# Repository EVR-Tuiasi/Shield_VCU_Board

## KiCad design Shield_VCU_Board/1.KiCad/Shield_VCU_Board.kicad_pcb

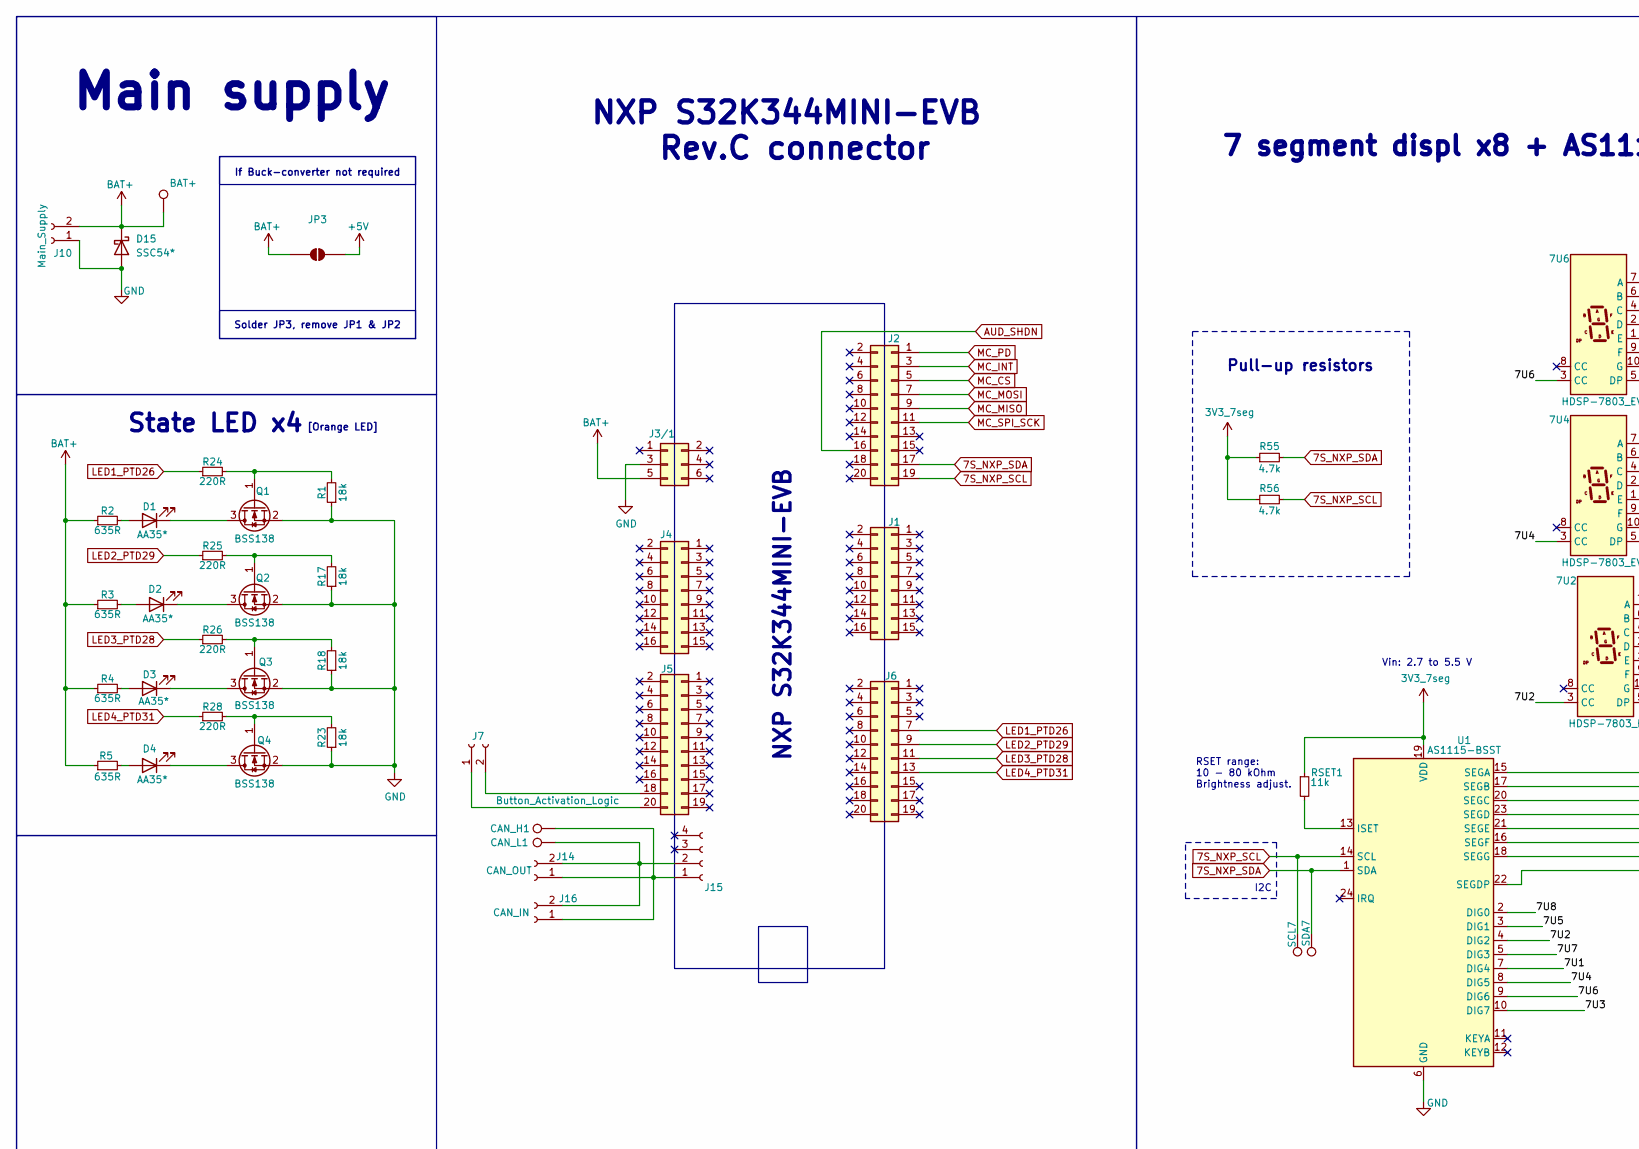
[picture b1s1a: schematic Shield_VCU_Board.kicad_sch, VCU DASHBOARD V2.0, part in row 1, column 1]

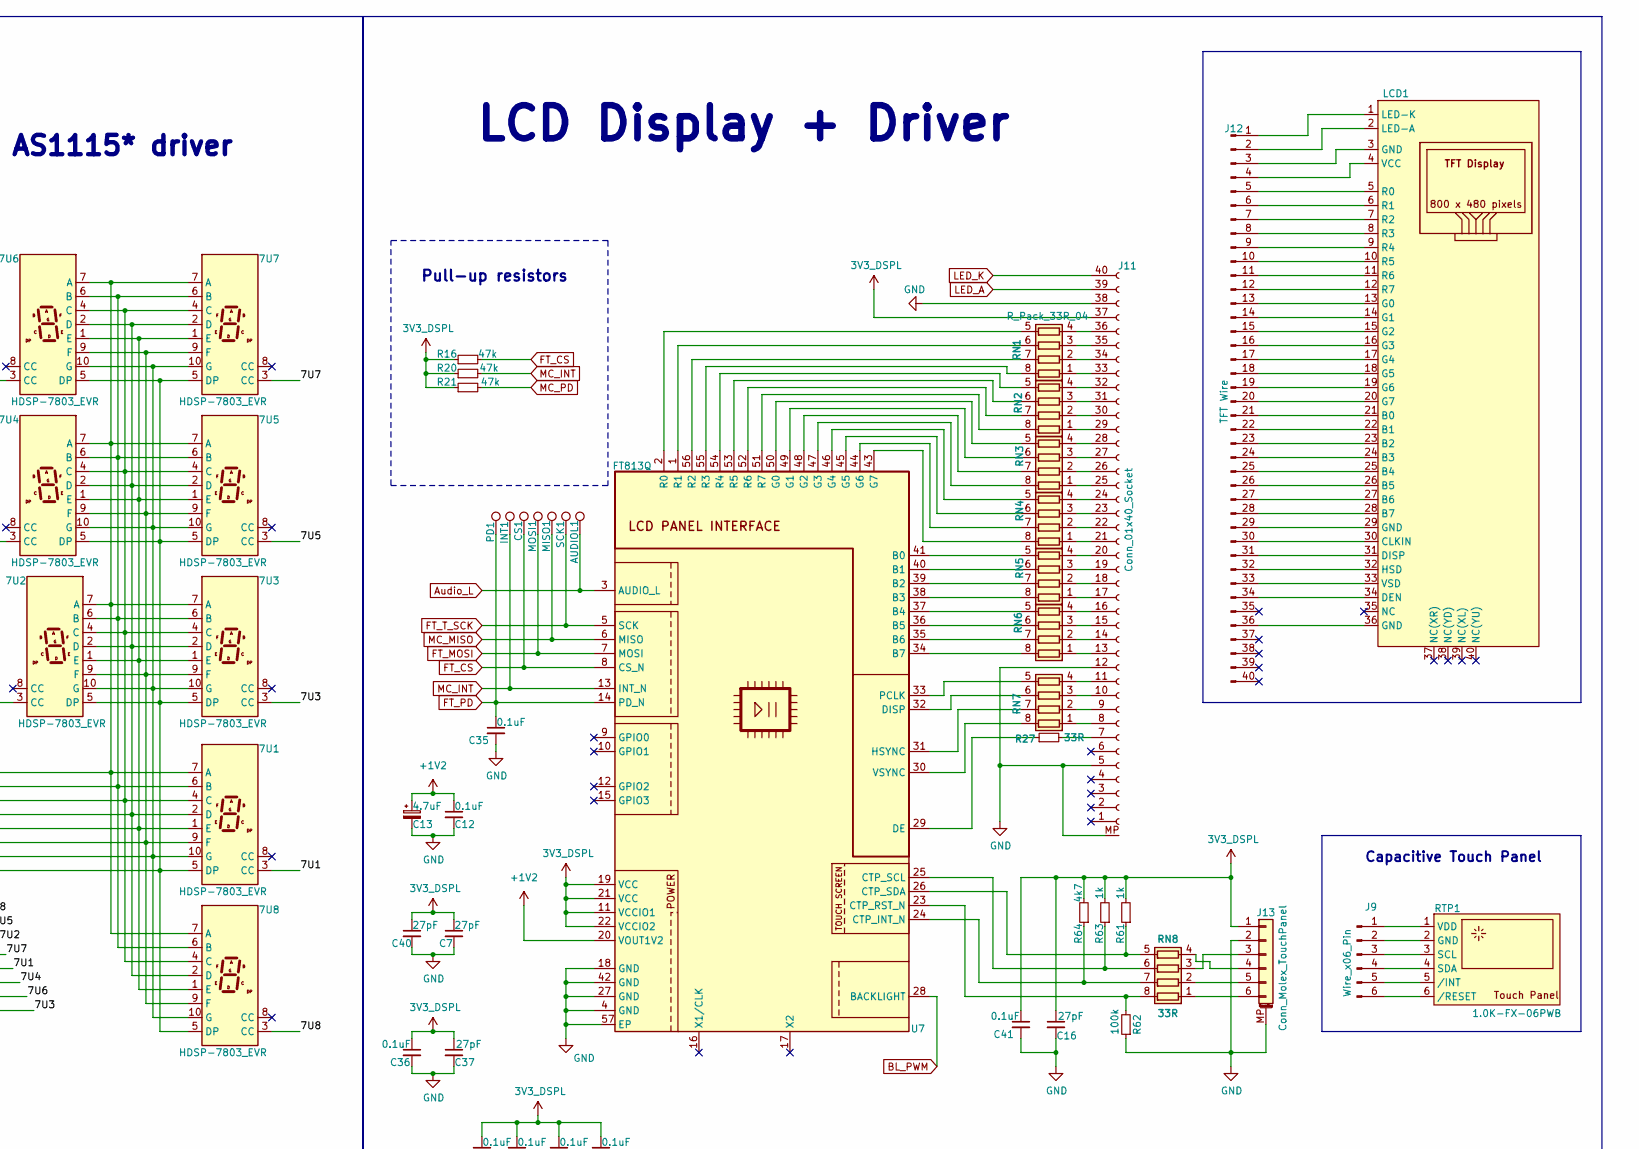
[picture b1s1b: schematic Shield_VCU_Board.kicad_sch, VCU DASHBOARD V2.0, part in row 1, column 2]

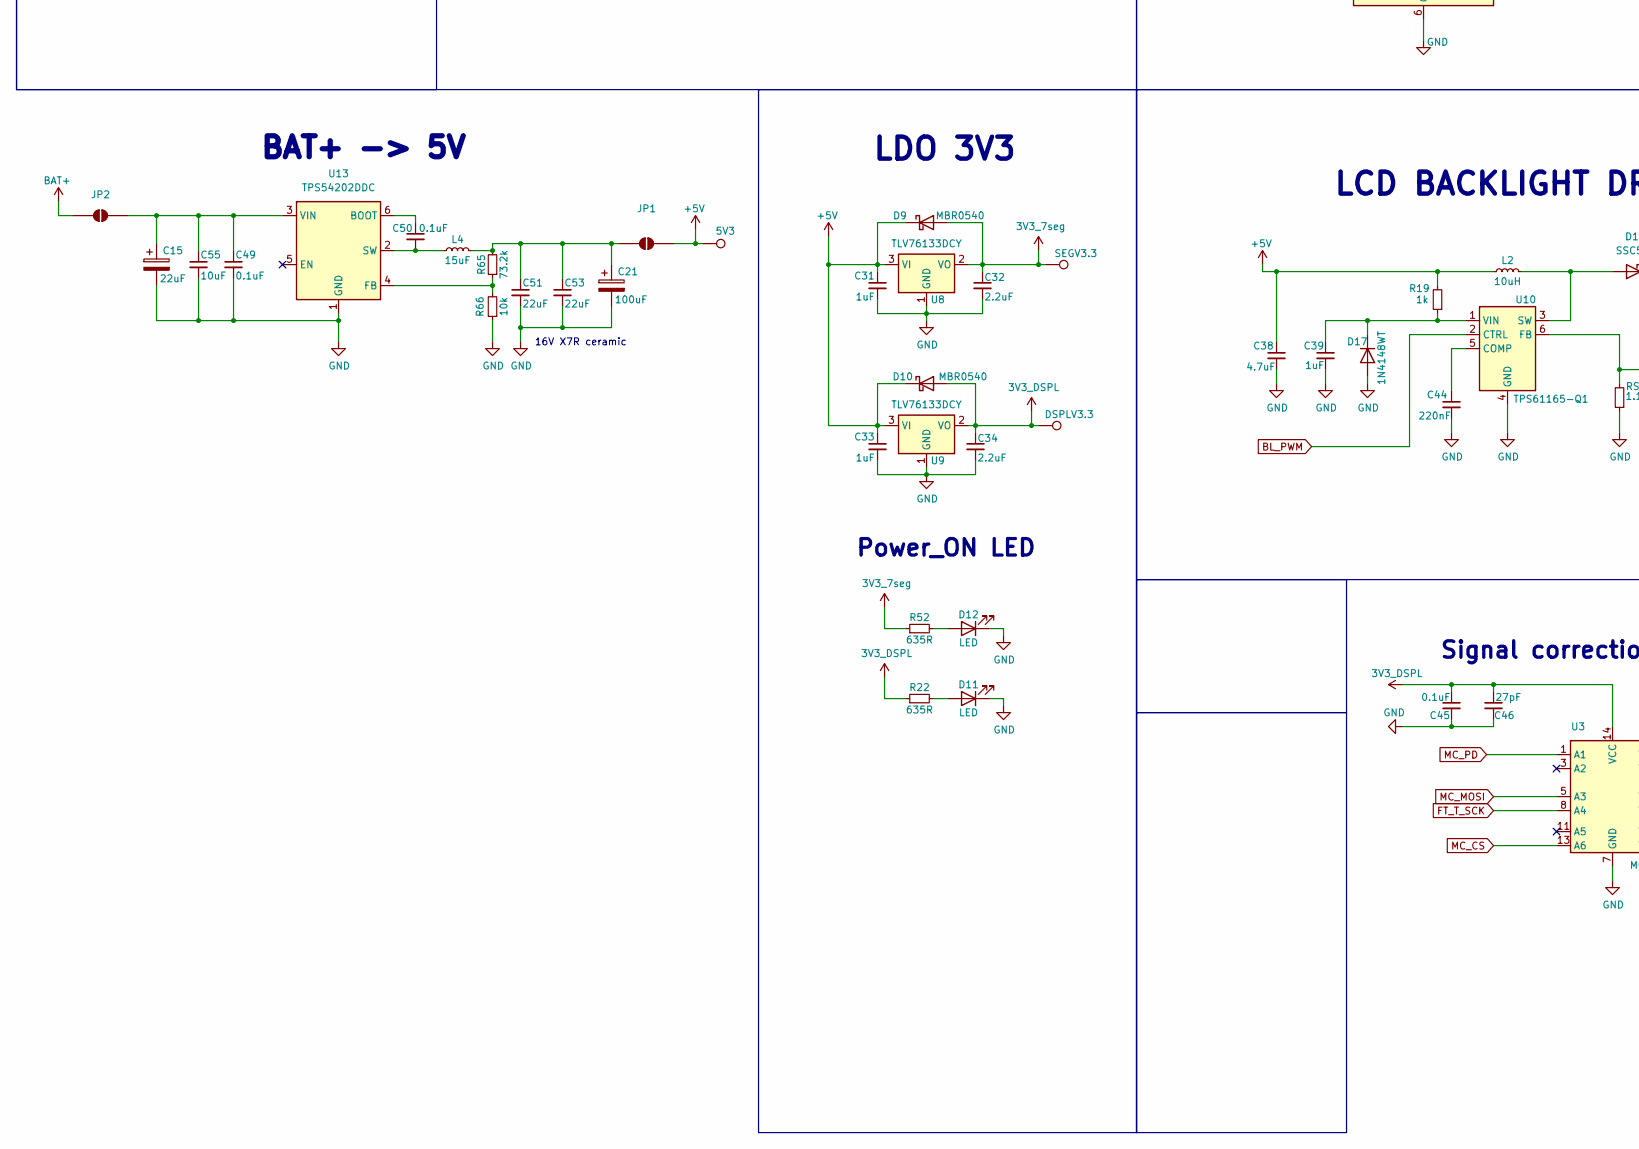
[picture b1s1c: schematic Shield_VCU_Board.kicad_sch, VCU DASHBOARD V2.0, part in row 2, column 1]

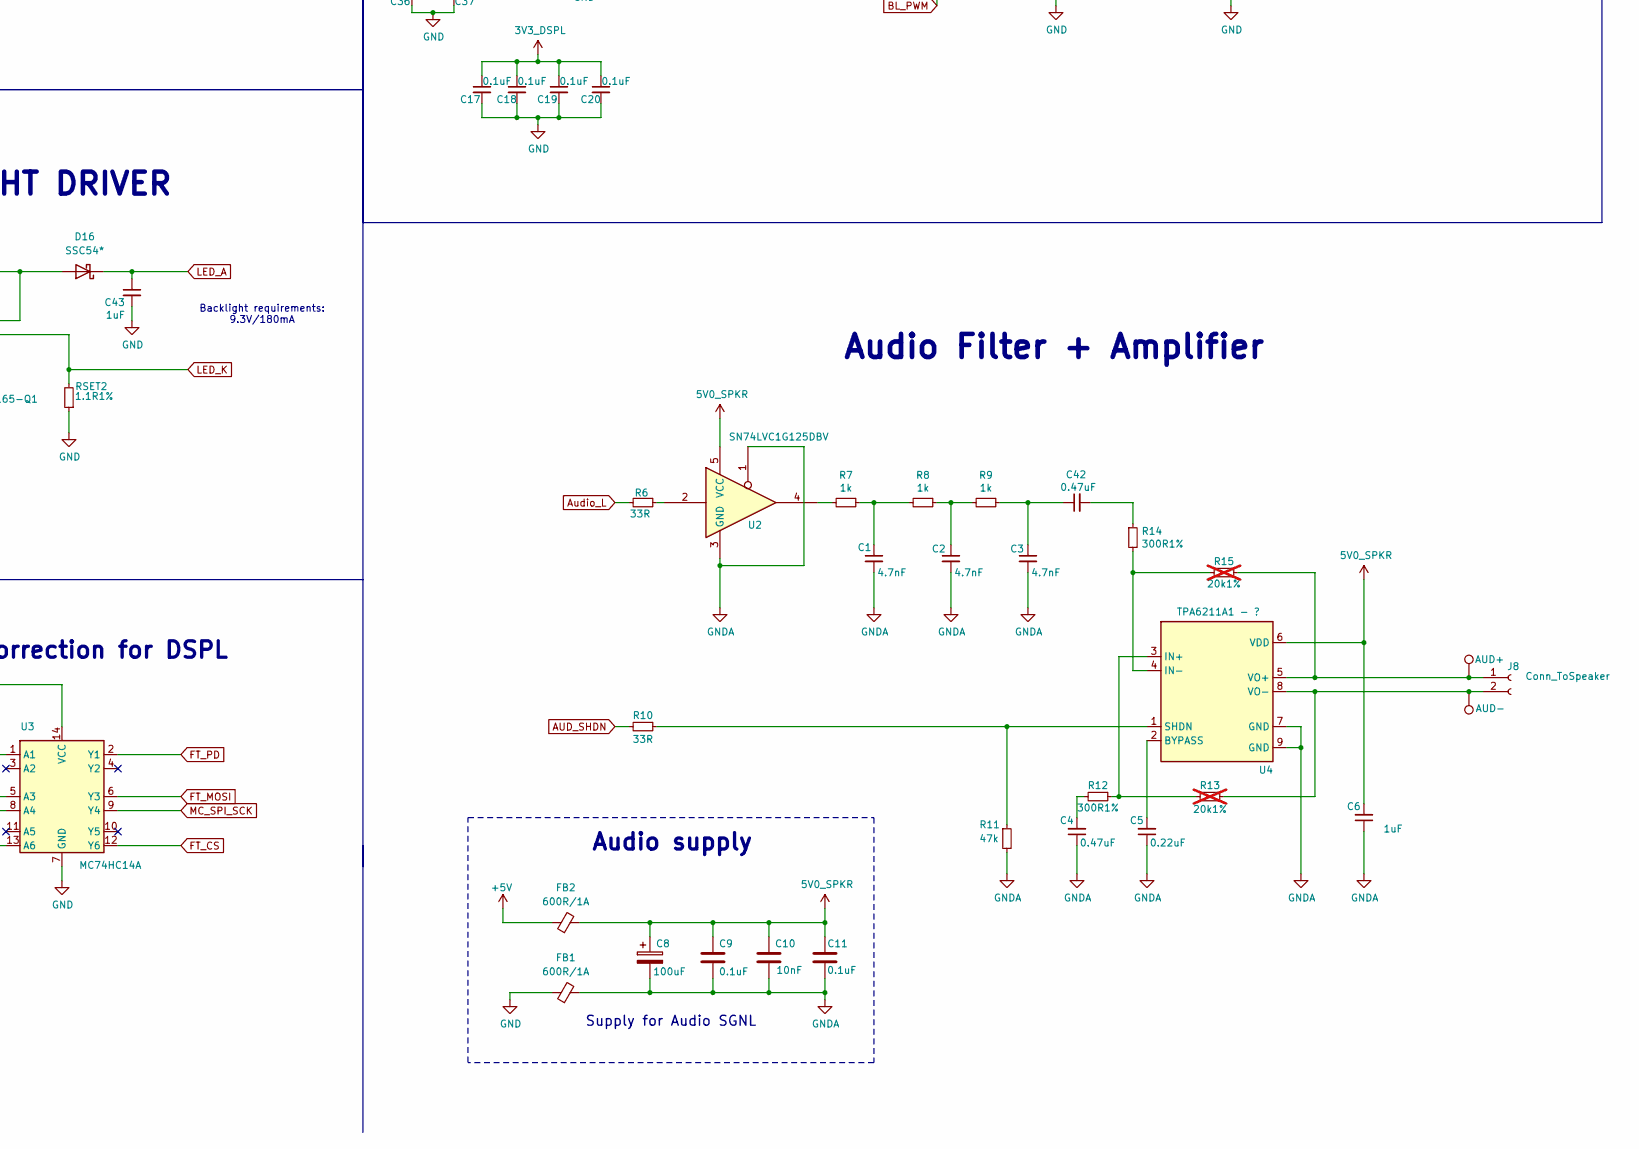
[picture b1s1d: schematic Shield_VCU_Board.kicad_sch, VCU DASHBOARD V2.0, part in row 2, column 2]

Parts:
5V3: 5V3; TestPoint_Pad_D1.0mm
7U1, 7U2, 7U3, 7U4, 7U5, 7U6, 7U7, 7U8: HDSP-7803_EVR; T7DS052BC
AUD+01: AUD+; TestPoint_Pad_D1.0mm
AUD-01: AUD-; TestPoint_Pad_D1.0mm
AUDIOL1: TestPoint; TestPoint_Pad_D1.0mm
BAT+01: BAT+; TestPoint_Pad_D1.0mm
C1, C2, C3: 4.7nF; C_0805_2012Metric_Pad1.18x1.45mm_HandSolder
C4, C42: 0.47uF; C_0805_2012Metric_Pad1.18x1.45mm_HandSolder
C5: 0.22uF; C_0805_2012Metric_Pad1.18x1.45mm_HandSolder
C6, C31, C33, C39, C43: 1uF; C_0805_2012Metric_Pad1.18x1.45mm_HandSolder
C7, C16, C37, C40, C46: 27pF; C_0805_2012Metric_Pad1.18x1.45mm_HandSolder
C8, C21: 100uF; CP_Elec_5x5.4
C9, C11, C12, C17, C18, C19, C20, C35, C36, C41, C45, C49, C50: 0.1uF; C_0805_2012Metric_Pad1.18x1.45mm_HandSolder
C10: 10nF; C_0805_2012Metric_Pad1.18x1.45mm_HandSolder
C13: 4.7uF; CP_EIA-2012-12_Kemet-R_HandSolder
C15: 22uF; CP_Elec_5x5.4
C32, C34: 2.2uF; C_0805_2012Metric_Pad1.18x1.45mm_HandSolder
C38: 4.7uF; C_0805_2012Metric_Pad1.18x1.45mm_HandSolder
C44: 220nF; C_0805_2012Metric_Pad1.18x1.45mm_HandSolder
C51, C53: 22uF; C_1210_3225Metric_Pad1.33x2.70mm_HandSolder
C55: 10uF; C_1210_3225Metric_Pad1.33x2.70mm_HandSolder
CAN_H1: TestPoint; TestPoint_Pad_D1.0mm
CAN_L1: TestPoint; TestPoint_Pad_D1.0mm
CS1: TestPoint; TestPoint_Pad_D1.0mm
D1, D2, D3, D4: AA35*; LED_Cree-PLCC4_3.2x2.8mm_CCW_Orange
D9, D10: MBR0540; D_SOD-123
D11, D12: LED; LED_0805_2012Metric
D15, D16: SSC54*; D_SMC
D17: 1N4148WT; D_SOD-123
DSPLV3.3: TestPoint; TestPoint_Pad_D1.0mm
FB1, FB2: 600R/1A; L_1206_3216Metric_Pad1.22x1.90mm_HandSolder
INT1: TestPoint; TestPoint_Pad_D1.0mm
J1, J4: Conn_02x08_Odd_Even; PinHeader_2x08_P2.54mm_Vertical_SMD
J2, J5, J6: Conn_02x10_Odd_Even; PinHeader_2x10_P2.54mm_Vertical_SMD
J3/1: NXP3; PinHeader_2x03_P2.54mm_Vertical_SMD
J7: Button_Activation_Logic; JST_PH_B2B-PH-K_1x02_P2.00mm_Vertical
J8: Conn_ToSpeaker; JST_PH_B2B-PH-K_1x02_P2.00mm_Vertical
J9: Wire_x06_Pin
J10: Main_Supply; JST_XH_B2B-XH-A_1x02_P2.50mm_Vertical
J11: Conn_01x40_Socket; Amphenol_F32Q-1A7x1-11040_1x40-1MP_P0.5mm_Horizontal
J12: TFT Wire
J13: Conn_Molex_TouchPanel; Molex_200528-0060_1x06-1MP_P1.00mm_Horizontal
J14: CAN_OUT; JST_PH_B2B-PH-K_1x02_P2.00mm_Vertical
J15: Conn_01x04_Socket; PinHeader_1x04_P2.54mm_Vertical
J16: CAN_IN; JST_PH_B2B-PH-K_1x02_P2.00mm_Vertical
JP1, JP2: SolderJumper_2_Open; SolderJumper-2_P1.3mm_Open_RoundedPad1.0x1.5mm
JP3: SolderJumper_2_Open; SolderJumper-2_P1.3mm_Open_TrianglePad1.0x1.5mm
L2: 10uH; L_Pulse_PA4340
L4: 15uF; L_Coilcraft_LPS4018
LCD1: LCD screen
MISO1: TestPoint; TestPoint_Pad_D1.0mm
MOSI1: TestPoint; TestPoint_Pad_D1.0mm
PD1: TestPoint; TestPoint_Pad_D1.0mm
Q1, Q2, Q3, Q4: BSS138; SOT-23
R1, R17, R18, R23: 18k; R_1206_3216Metric_Pad1.30x1.75mm_HandSolder
R2, R3, R4, R5, R22, R52: 635R; R_1206_3216Metric_Pad1.30x1.75mm_HandSolder
R6, R10: 33R; R_1206_3216Metric_Pad1.30x1.75mm_HandSolder
R7, R8, R9, R19, R61, R63: 1k; R_1206_3216Metric_Pad1.30x1.75mm_HandSolder
R11, R16, R20, R21: 47k; R_1206_3216Metric_Pad1.30x1.75mm_HandSolder
R12, R14: 300R1%; R_1206_3216Metric_Pad1.30x1.75mm_HandSolder
R13, R15: 20k1%; R_1206_3216Metric_Pad1.30x1.75mm_HandSolder; not fitted
R24, R25, R26, R28: 220R; R_1206_3216Metric_Pad1.30x1.75mm_HandSolder
R27: 33R; R_0603_1608Metric_Pad0.98x0.95mm_HandSolder
R55, R56: 4.7k; R_1206_3216Metric_Pad1.30x1.75mm_HandSolder
R62: 100k; R_1206_3216Metric_Pad1.30x1.75mm_HandSolder
R64: 4k7; R_1206_3216Metric_Pad1.30x1.75mm_HandSolder
R65: 73.2k; R_1206_3216Metric_Pad1.30x1.75mm_HandSolder
R66: 10k; R_1206_3216Metric_Pad1.30x1.75mm_HandSolder
RN1, RN2, RN3, RN4, RN5, RN6, RN7: R_Pack_33R_04; R_Array_Convex_4x0402
RN8: 33R; R_Array_Convex_4x0402
RSET1: 11k; R_1206_3216Metric_Pad1.30x1.75mm_HandSolder
RSET2: 1.1R1%; R_1206_3216Metric_Pad1.30x1.75mm_HandSolder
RTP1: 1.0K-FX-06PWB
SCK1: TestPoint; TestPoint_Pad_D1.0mm
SCL7: TestPoint; TestPoint_Pad_D1.0mm
SDA7: TestPoint; TestPoint_Pad_D1.0mm
SEGV3.3: TestPoint; TestPoint_Pad_D1.0mm
U1: AS1115-BSST; QSOP-24_3.9x8.7mm_P0.635mm
U2: SN74LVC1G125DBV; SOT-23-5
U3: MC74HC14A; SOIC-14_3.9x8.7mm_P1.27mm
U4: TPA6211A1 - ?; SOP65P490X110-9L
U7: FT813Q; LFCSP-56-1EP_8x8mm_P0.5mm_EP6.6x6.6mm
U8, U9: TLV76133DCY; SOT-223-3_TabPin2
U10: TPS61165-Q1; SOT-23-6
U13: TPS54202DDC; SOT-23-6

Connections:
3V3_7seg: C32.1, D9.2 (A), R52.1, R55.1, R56.1, RSET1.1, SEGV3.3.1 (1_1), U1.19 (VDD), U8.2 (VO)
3V3_DSPL: C7.1, C16.1, C17.1, C18.1, C19.1, C20.1, C34.1, C36.1, C37.1, C40.1, C41.1, C45.1, C46.1, D10.2 (A), DSPLV3.3.1 (1_1), J11.37 (Pin_4), J13.1, R16.1, R20.1, R21.1, R22.1, R61.2, R63.2, R64.2, U3.14 (VCC), U7.11 (VCCIO1), U7.19 (VCC), U7.21 (VCC), U7.22 (VCCIO2), U9.2 (VO)
5V0_SPKR: C6.2, C8.1, C9.2, C10.2, C11.2, FB2.2, U2.5 (VCC), U4.6 (VDD)
7S_NXP_SCL: J2.19, R56.2, SCL7.1 (1_1), U1.14 (SCL)
7S_NXP_SDA: J2.17, R55.2, SDA7.1 (1_1), U1.1 (SDA)
+1V2: C12.1, C13.1, U7.20 (VOUT1V2)
+5V: 5V3.1 (1_1), C31.1, C33.1, C38.1, D9.1 (K), D10.1 (K), FB2.1, JP1.2 (B), JP3.2 (B), L2.1, R19.2, U8.3 (VI), U9.3 (VI)
/7U1: 7U1.3 (CC), U1.7 (DIG4)
/7U2: 7U2.3 (CC), U1.4 (DIG2)
/7U3: 7U3.3 (CC), U1.10 (DIG7)
/7U4: 7U4.3 (CC), U1.8 (DIG5)
/7U5: 7U5.3 (CC), U1.3 (DIG1)
/7U6: 7U6.3 (CC), U1.9 (DIG6)
/7U7: 7U7.3 (CC), U1.5 (DIG3)
/7U8: 7U8.3 (CC), U1.2 (DIG0)
AUD_SHDN: J2.16, R10.2
Audio_L: AUDIOL1.1 (1_1), R6.2, U7.3 (AUDIO_L)
BAT+: BAT+01.1 (1_1), D15.1 (K), J3/1.5, J10.2, JP2.1 (A), JP3.1 (A), R2.1, R3.1, R4.1, R5.1
BL_PWM: U7.28 (BACKLIGHT), U10.2 (CTRL)
FT_CS: CS1.1 (1_1), R16.2, U3.12 (Y6), U7.8 (CS_N)
FT_MOSI: MOSI1.1 (1_1), U3.6 (Y3), U7.7 (MOSI)
FT_PD: C35.1, PD1.1 (1_1), U3.2 (Y1), U7.14 (PD_N)
FT_T_SCK: SCK1.1 (1_1), U3.8 (A4), U7.5 (SCK)
GND: C7.2, C12.2, C13.2, C15.2, C16.2, C17.2, C18.2, C19.2, C20.2, C21.2, C31.2, C32.2, C33.2, C34.2, C35.2, C36.2, C37.2, C38.2, C39.2, C40.2, C41.2, C43.2, C44.2, C45.2, C46.2, C49.2, C51.2, C53.2, C55.2, D11.1 (K), D12.1 (K), D15.2 (A), D17.2 (A), FB1.1, J3/1.3, J10.1, J11.5 (Pin_36), J11.12 (Pin_29), J11.38 (Pin_3), J11.MP, J13.2, J13.MP (MountPin), Q1.2 (S), Q2.2 (S), Q3.2 (S), Q4.2 (S), R1.1, R17.1, R18.1, R23.1, R62.1, R66.1, RSET2.1, U1.6 (GND), U3.7 (GND), U7.4 (GND), U7.18 (GND), U7.27 (GND), U7.42 (GND), U7.57 (EP), U8.1 (GND), U9.1 (GND), U10.4 (GND), U13.1 (GND)
GNDA: C1.2, C2.2, C3.2, C4.1, C5.1, C6.1, C8.2, C9.1, C10.1, C11.1, FB1.2, R11.2, U2.1, U2.3 (GND), U4.7 (GND), U4.9 (GND)
LED1_PTD26: J6.7, R24.1
LED2_PTD29: J6.9, R25.1
LED3_PTD28: J6.11, R26.1
LED4_PTD31: J6.13, R28.1
LED_A: C43.1, D16.1 (K), J11.39 (Pin_2)
LED_K: J11.40 (Pin_1), RSET2.2, U10.6 (FB)
MC_CS: J2.5, U3.13 (A6)
MC_INT: INT1.1 (1_1), J2.3, R20.2, U7.13 (INT_N)
MC_MISO: J2.9, MISO1.1 (1_1), U7.6 (MISO)
MC_MOSI: J2.7, U3.5 (A3)
MC_PD: J2.1, R21.2, U3.1 (A1)
MC_SPI_SCK: J2.11, U3.9 (Y4)
unnamed: 7U1.7 (A), 7U2.7 (A), 7U3.7 (A), 7U4.7 (A), 7U5.7 (A), 7U6.7 (A), 7U7.7 (A), 7U8.7 (A), U1.15 (SEGA)
unnamed: 7U1.6 (B), 7U2.6 (B), 7U3.6 (B), 7U4.6 (B), 7U5.6 (B), 7U6.6 (B), 7U7.6 (B), 7U8.6 (B), U1.17 (SEGB)
unnamed: 7U1.4 (C), 7U2.4 (C), 7U3.4 (C), 7U4.4 (C), 7U5.4 (C), 7U6.4 (C), 7U7.4 (C), 7U8.4 (C), U1.20 (SEGC)
unnamed: 7U1.2 (D), 7U2.2 (D), 7U3.2 (D), 7U4.2 (D), 7U5.2 (D), 7U6.2 (D), 7U7.2 (D), 7U8.2 (D), U1.23 (SEGD)
unnamed: 7U1.5 (DP), 7U2.5 (DP), 7U3.5 (DP), 7U4.5 (DP), 7U5.5 (DP), 7U6.5 (DP), 7U7.5 (DP), 7U8.5 (DP), U1.22 (SEGDP)
unnamed: 7U1.1 (E), 7U2.1 (E), 7U3.1 (E), 7U4.1 (E), 7U5.1 (E), 7U6.1 (E), 7U7.1 (E), 7U8.1 (E), U1.21 (SEGE)
unnamed: 7U1.9 (F), 7U2.9 (F), 7U3.9 (F), 7U4.9 (F), 7U5.9 (F), 7U6.9 (F), 7U7.9 (F), 7U8.9 (F), U1.16 (SEGF)
unnamed: 7U1.10 (G), 7U2.10 (G), 7U3.10 (G), 7U4.10 (G), 7U5.10 (G), 7U6.10 (G), 7U7.10 (G), 7U8.10 (G), U1.18 (SEGG)
unnamed: C1.1, R7.1, R8.2
unnamed: C2.1, R8.1, R9.2
unnamed: C3.1, C42.1, R9.1
unnamed: C4.2, R12.2
unnamed: C42.2, R14.1
unnamed: D1.2 (A), R2.2
unnamed: D1.1 (K), Q1.3 (D)
unnamed: D2.2 (A), R3.2
unnamed: D2.1 (K), Q2.3 (D)
unnamed: D3.2 (A), R4.2
unnamed: D3.1 (K), Q3.3 (D)
unnamed: D4.2 (A), R5.2
unnamed: D4.1 (K), Q4.3 (D)
unnamed: D11.2 (A), R22.2
unnamed: D12.2 (A), R52.2
unnamed: D16.2 (A), L2.2, U10.3 (SW)
unnamed: C39.1, D17.1 (K), R19.1, U10.1 (VIN)
unnamed: J5.18, J7.2
unnamed: J5.20, J7.1
unnamed: AUD+01.1 (1_1), J8.1, R15.1, U4.5 (VO+)
unnamed: AUD-01.1 (1_1), J8.2, R13.1, U4.8 (VO-)
unnamed: J9.1, RTP1.1 (VDD)
unnamed: J9.2, RTP1.2 (GND)
unnamed: J9.3, RTP1.3 (SCL)
unnamed: J9.4, RTP1.4 (SDA)
unnamed: J9.5, RTP1.5 (/INT)
unnamed: J9.6, RTP1.6 (/RESET)
unnamed: J11.36 (Pin_5), RN1.4 (R4.1)
unnamed: J11.35 (Pin_6), RN1.3 (R3.1)
unnamed: J11.34 (Pin_7), RN1.2 (R2.1)
unnamed: J11.33 (Pin_8), RN1.1 (R1.1)
unnamed: J11.32 (Pin_9), RN2.4 (R4.1)
unnamed: J11.31 (Pin_10), RN2.3 (R3.1)
unnamed: J11.30 (Pin_11), RN2.2 (R2.1)
unnamed: J11.29 (Pin_12), RN2.1 (R1.1)
unnamed: J11.28 (Pin_13), RN3.4 (R4.1)
unnamed: J11.27 (Pin_14), RN3.3 (R3.1)
unnamed: J11.26 (Pin_15), RN3.2 (R2.1)
unnamed: J11.25 (Pin_16), RN3.1 (R1.1)
unnamed: J11.24 (Pin_17), RN4.4 (R4.1)
unnamed: J11.23 (Pin_18), RN4.3 (R3.1)
unnamed: J11.22 (Pin_19), RN4.2 (R2.1)
unnamed: J11.21 (Pin_20), RN4.1 (R1.1)
unnamed: J11.20 (Pin_21), RN5.4 (R4.1)
unnamed: J11.19 (Pin_22), RN5.3 (R3.1)
unnamed: J11.18 (Pin_23), RN5.2 (R2.1)
unnamed: J11.17 (Pin_24), RN5.1 (R1.1)
unnamed: J11.16 (Pin_25), RN6.4 (R4.1)
unnamed: J11.15 (Pin_26), RN6.3 (R3.1)
unnamed: J11.14 (Pin_27), RN6.2 (R2.1)
unnamed: J11.13 (Pin_28), RN6.1 (R1.1)
unnamed: J11.11 (Pin_30), RN7.4 (R4.1)
unnamed: J11.10 (Pin_31), RN7.3 (R3.1)
unnamed: J11.9 (Pin_32), RN7.2 (R2.1)
unnamed: J11.8 (Pin_33), RN7.1 (R1.1)
unnamed: J11.7 (Pin_34), R27.2
unnamed: J12.1, LCD1.1 (LED-K)
unnamed: J12.2, LCD1.2 (LED-A)
unnamed: J12.3, LCD1.3 (GND)
unnamed: J12.4, LCD1.4 (VCC)
unnamed: J12.5, LCD1.5 (R0)
unnamed: J12.6, LCD1.6 (R1)
unnamed: J12.7, LCD1.7 (R2)
unnamed: J12.8, LCD1.8 (R3)
unnamed: J12.9, LCD1.9 (R4)
unnamed: J12.10, LCD1.10 (R5)
unnamed: J12.11, LCD1.11 (R6)
unnamed: J12.12, LCD1.12 (R7)
unnamed: J12.13, LCD1.13 (G0)
unnamed: J12.14, LCD1.14 (G1)
unnamed: J12.15, LCD1.15 (G2)
unnamed: J12.16, LCD1.16 (G3)
unnamed: J12.17, LCD1.17 (G4)
unnamed: J12.18, LCD1.18 (G5)
unnamed: J12.19, LCD1.19 (G6)
unnamed: J12.20, LCD1.20 (G7)
unnamed: J12.21, LCD1.21 (B0)
unnamed: J12.22, LCD1.22 (B1)
unnamed: J12.23, LCD1.23 (B2)
unnamed: J12.24, LCD1.24 (B3)
unnamed: J12.25, LCD1.25 (B4)
unnamed: J12.26, LCD1.26 (B5)
unnamed: J12.27, LCD1.27 (B6)
unnamed: J12.28, LCD1.28 (B7)
unnamed: J12.29, LCD1.29 (GND)
unnamed: J12.30, LCD1.30 (CLKIN)
unnamed: J12.31, LCD1.31 (DISP)
unnamed: J12.32, LCD1.32 (HSD)
unnamed: J12.33, LCD1.33 (VSD)
unnamed: J12.34, LCD1.34 (DEN)
unnamed: J12.36, LCD1.36 (GND)
unnamed: J13.3, RN8.3 (R3.1)
unnamed: J13.4, RN8.4 (R4.1)
unnamed: J13.5, RN8.2 (R2.1)
unnamed: J13.6, RN8.1 (R1.1)
unnamed: CAN_H1.1 (1_1), J14.1, J15.1, J16.1
unnamed: CAN_L1.1 (1_1), J14.2, J15.2, J16.2
unnamed: C21.1, C51.1, C53.1, JP1.1 (A), L4.2, R65.2
unnamed: C15.1, C49.1, C55.1, JP2.2 (B), U13.3 (VIN)
unnamed: Q1.1 (G), R1.2, R24.2
unnamed: Q2.1 (G), R17.2, R25.2
unnamed: Q3.1 (G), R18.2, R26.2
unnamed: Q4.1 (G), R23.2, R28.2
unnamed: R6.1, U2.2
unnamed: R7.2, U2.4
unnamed: RN1.8 (R1.2), U7.55 (R3)
unnamed: RN1.7 (R2.2), U7.56 (R2)
unnamed: RN1.6 (R3.2), U7.1 (R1)
unnamed: RN1.5 (R4.2), U7.2 (R0)
unnamed: RN2.8 (R1.2), U7.51 (R7)
unnamed: RN2.7 (R2.2), U7.52 (R6)
unnamed: RN2.6 (R3.2), U7.53 (R5)
unnamed: RN2.5 (R4.2), U7.54 (R4)
unnamed: RN3.8 (R1.2), U7.47 (G3)
unnamed: RN3.7 (R2.2), U7.48 (G2)
unnamed: RN3.6 (R3.2), U7.49 (G1)
unnamed: RN3.5 (R4.2), U7.50 (G0)
unnamed: RN4.8 (R1.2), U7.43 (G7)
unnamed: RN4.7 (R2.2), U7.44 (G6)
unnamed: RN4.6 (R3.2), U7.45 (G5)
unnamed: RN4.5 (R4.2), U7.46 (G4)
unnamed: RN5.8 (R1.2), U7.38 (B3)
unnamed: RN5.7 (R2.2), U7.39 (B2)
unnamed: RN5.6 (R3.2), U7.40 (B1)
unnamed: RN5.5 (R4.2), U7.41 (B0)
unnamed: RN6.8 (R1.2), U7.34 (B7)
unnamed: RN6.7 (R2.2), U7.35 (B6)
unnamed: RN6.6 (R3.2), U7.36 (B5)
unnamed: RN6.5 (R4.2), U7.37 (B4)
unnamed: RN7.8 (R1.2), U7.30 (VSYNC)
unnamed: RN7.7 (R2.2), U7.31 (HSYNC)
unnamed: RN7.6 (R3.2), U7.32 (DISP)
unnamed: RN7.5 (R4.2), U7.33 (PCLK)
unnamed: R62.2, RN8.8 (R1.2), U7.23 (CTP_RST_N)
unnamed: R64.1, RN8.7 (R2.2), U7.24 (CTP_INT_N)
unnamed: R63.1, RN8.6 (R3.2), U7.25 (CTP_SCL)
unnamed: R61.1, RN8.5 (R4.2), U7.26 (CTP_SDA)
unnamed: RSET1.2, U1.13 (ISET)
unnamed: C5.2, U4.2 (BYPASS)
unnamed: R12.1, R13.2, U4.3 (IN+)
unnamed: R14.2, R15.2, U4.4 (IN-)
unnamed: R10.1, R11.1, U4.1 (SHDN)
unnamed: R27.1, U7.29 (DE)
unnamed: C44.1, U10.5 (COMP)
unnamed: C50.1, U13.6 (BOOT)
unnamed: R65.1, R66.2, U13.4 (FB)
unnamed: C50.2, L4.1, U13.2 (SW)

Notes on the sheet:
LDO 3V3
If Buck-converter not required
Capacitive Touch Panel
Vin: 2.7 to 5.5 V
Pull-up resistors
NXP S32K344MINI-EVB Rev.C connector
State LED x4
Backlight requirements: 9.3V/180mA
LCD BACKLIGHT DRIVER
Audio supply
BAT+ -> 5V
Signal correction for DSPL
Solder JP3, remove JP1 & JP2
LCD Display + Driver
16V X7R ceramic
Audio Filter + Amplifier
7 segment displ x8 + AS1115* driver
Power_ON LED
I2C
NXP S32K344MINI-EVB
Main supply
Supply for Audio SGNL
RSET range: 10 - 80 kOhm Brightness adjust.
[Orange LED]

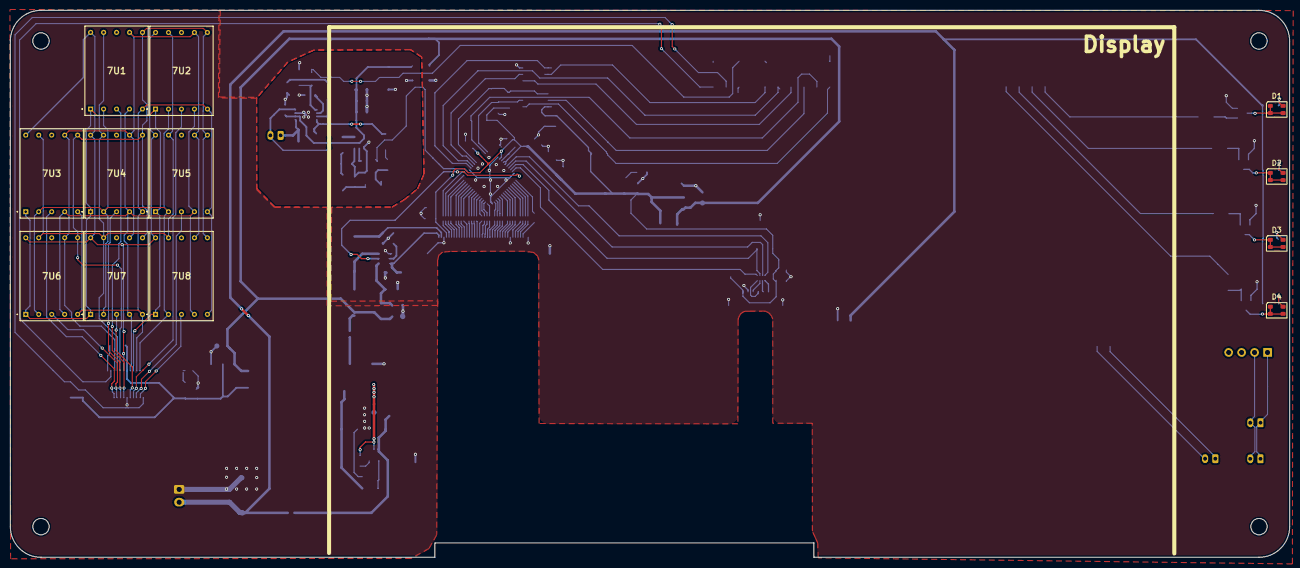
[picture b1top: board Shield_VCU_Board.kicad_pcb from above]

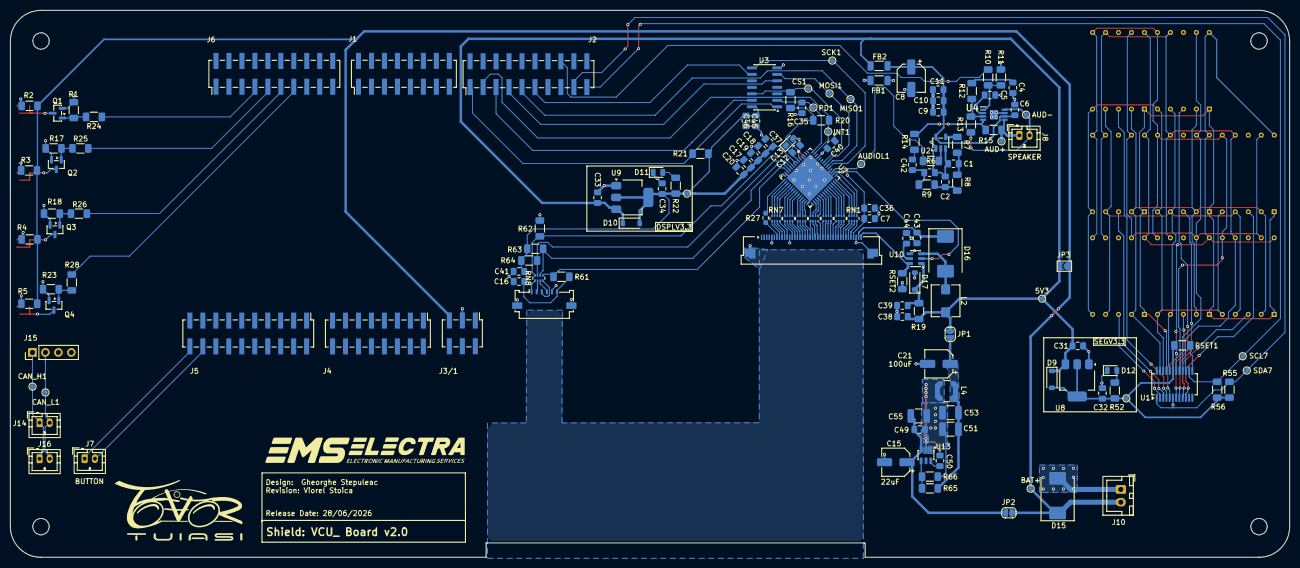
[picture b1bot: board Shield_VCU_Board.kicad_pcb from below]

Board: 2 copper layers, 250.5 x 107.1 mm, 158 parts (146 on the bottom side), 151 nets.

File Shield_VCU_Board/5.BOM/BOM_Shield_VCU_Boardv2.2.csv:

Reference,Qty,Value,Footprint,Part Nr.,Manufacturer
"7U1,7U2,7U3,7U4,7U5,7U6,7U7,7U8",8,HDSP-7803_EVR,GHSTProj:T7DS052BC,157136B12701,Wurth Elektronik
"C1,C2,C3",3,4.7nF,Capacitor_SMD:C_0805_2012Metric_Pad1.18x1.45mm_HandSolder,08052C223M4Z2A,KYOCERA AVX
"C4,C42",2,0.47uF,Capacitor_SMD:C_0805_2012Metric_Pad1.18x1.45mm_HandSolder,0805ZD474KAT2A,KYOCERA AVX
C5,1,0.22uF,Capacitor_SMD:C_0805_2012Metric_Pad1.18x1.45mm_HandSolder,0805ZC224KAT2A,KYOCERA AVX
"C6,C27,C29,C31,C33,C39,C43",5,1uF,Capacitor_SMD:C_0805_2012Metric_Pad1.18x1.45mm_HandSolder,08053G105MAT2A,KYOCERA AVX
"C7,C16,C37,C40",5,27pF,Capacitor_SMD:C_0805_2012Metric_Pad1.18x1.45mm_HandSolder,VJ0805A270GXJCW1BC,Vishay/Vitramon
C8,2,100uF,Capacitor_SMD:CP_Elec_5x5.4,8.6506E+11,Wurth Elektronik
"C9,C11,C12,C17,C18,C19,C20,C35,C36,C41,C45,C49,C50,C54",13,0.1uF,Capacitor_SMD:C_0805_2012Metric_Pad1.18x1.45mm_HandSolder,KAM21BR71H104JM,KYOCERA AVX
C10,1,10nF,Capacitor_SMD:C_0805_2012Metric_Pad1.18x1.45mm_HandSolder,GRM21BR7LU103KW01L,Murata Electronics
"C13,C38",2,4.7uF,"Capacitor_SMD:C_0805_2012Metric_Pad1.18x1.45mm_HandSolder,Capacitor_Tantalum_SMD:CP_EIA-2012-12_Kemet-R_HandSolder",GCM21BM8EH475KE08L,Murata Electronics
C15,1,22uF,,8.65231E+11,Wurth Elektronik
"C51,C53",2,22uF,,C3225X7R1C226K250AC,TDK
"C28,C30,C32,C34",2,2.2uF,Capacitor_SMD:C_0805_2012Metric_Pad1.18x1.45mm_HandSolder,GXT21BR71C225KE01L,Murata Electronics
C44,1,220nF,Capacitor_SMD:C_0805_2012Metric_Pad1.18x1.45mm_HandSolder,KAM21KR72A224KU,KYOCERA AVX
"C47,C55",1,10uF,Capacitor_SMD:C_1210_3225Metric_Pad1.33x2.70mm_HandSolder,12103C106K4T4A,KYOCERA AVX
"D1,D2,D3,D4",4,AA35*,ALibrary:LED_Cree-PLCC4_3.2x2.8mm_CCW_Orange,AA3527ASESK-50MAV,Kingbright
"D7,D8,D9,D10",4,MBR0540,Diode_SMD:D_SOD-123,MBR0540T1G,onsemi
"D11,D12,D13,D14",4,LED,LED_SMD:LED_0805_2012Metric,APTD2012LCGCK,Kingbright
"D15,D16",2,SSC54*,Diode_SMD:D_SMC,SSC54HE3_A/H,Vishay Semiconductors
D17,1,1N4148WT,Diode_SMD:D_SOD-123,1N4148WT,YAGEO
"FB1,FB2",2,600R/1A,Inductor_SMD:L_1206_3216Metric_Pad1.22x1.90mm_HandSolder,2512066017Y1,Fair-Rite
"L2,L3,L4",3,10uH,"Inductor_SMD:L_Coilcraft_LPS4018,Inductor_SMD:L_Pulse_PA4340",LPS4018-103MRC,Coilcraft
"Q1,Q2,Q3,Q4",4,BSS138,Package_TO_SOT_SMD:SOT-23,BSS138,onsemi
"R1,R17,R18,R23",4,18k,Resistor_SMD:R_1206_3216Metric_Pad1.30x1.75mm_HandSolder,,Avem la Garaj
"R3,R4,R5,R22,R52,R2",6,635R,Resistor_SMD:R_1206_3216Metric_Pad1.30x1.75mm_HandSolder,,Avem la Garaj
"R6,R10,R27,RN8",4,33R,"Resistor_SMD:R_0603_1608Metric_Pad0.98x0.95mm_HandSolder,Resistor_SMD:R_1206_3216Metric_Pad1.30x1.75mm_HandSolder,Resistor_SMD:R_Cat16-4",CRCW120633R0FKTA,Vishay
"R7,R8,R9,R19,R53,R54,R61,R63",8,1k,Resistor_SMD:R_1206_3216Metric_Pad1.30x1.75mm_HandSolder,CRCW12061K00JNECHP,Vishay
"R11,R16,R20,R21",4,47k,Resistor_SMD:R_1206_3216Metric_Pad1.30x1.75mm_HandSolder,CRCW120647K0JNEAHP,Vishay
"R12,R14",2,10k1%,Resistor_SMD:R_1206_3216Metric_Pad1.30x1.75mm_HandSolder,RCC120610K0FKEA,Vishay/Dale
"R13,R15",2,20k1%,Resistor_SMD:R_1206_3216Metric_Pad1.30x1.75mm_HandSolder,CRCW120620K0FKEAHP,Vishay
"R24,R25,R26,R28",4,220R,Resistor_SMD:R_1206_3216Metric_Pad1.30x1.75mm_HandSolder,CRCW1206220RFKEC,Vishay
"R55,R56",2,4.7k,Resistor_SMD:R_1206_3216Metric_Pad1.30x1.75mm_HandSolder,RE1206DRE074K7L,YAGEO
R59,1,523k,Resistor_SMD:R_1206_3216Metric_Pad1.30x1.75mm_HandSolder,RC1206FR-07523KL,YAGEO
"R60,R62,R66",1,100k,Resistor_SMD:R_1206_3216Metric_Pad1.30x1.75mm_HandSolder,CRCW1206100KFKEBC,Vishay
R64,1,4k7,Resistor_SMD:R_1206_3216Metric_Pad1.30x1.75mm_HandSolder,RE1206DRE074K7L,YAGEO
R65,1,73k2 .1%,Resistor_SMD:R_1206_3216Metric_Pad1.30x1.75mm_HandSolder,RP73D2B73K2BTDF,TE Connectivity / AMP
"RN1,RN2,RN3,RN4,RN5,RN6,RN7",7,R_Pack_33R_04,Resistor_SMD:R_Array_Convex_4x0402,RAVF104DJT33R0,SEI Stackpole
RSET1,1,11k,Resistor_SMD:R_1206_3216Metric_Pad1.30x1.75mm_HandSolder,CR1206-FX-1102ELF,Bourns
RSET2,1,1.1R1%,Resistor_SMD:R_1206_3216Metric_Pad1.30x1.75mm_HandSolder,CRCW12061R10FNEA,Vishay
U1,1,AS1115-BSST,Package_SO:QSOP-24_3.9x8.7mm_P0.635mm,AS1115-BSST,ams OSRAM
U2,1,SN74LVC1G125DBV,Package_TO_SOT_SMD:SOT-23-5,SN74LVC1G125DBVT,Texas Instruments
U3,1,MC74HC14A,Package_SO:SOIC-14_3.9x8.7mm_P1.27mm,MC74HC14ADR2G-Q,onsemi
U4,1,TPA6211A1 ,TPA:TPS73601DRBR,SLOS490TPA6205A1,Texas Instruments
"U5,U6",2,TLV76150DCY,Package_TO_SOT_SMD:SOT-223-3_TabPin2,TLV76150DCYR,Texas Instruments
U7,1,FT813Q,Package_CSP:LFCSP-56-1EP_8x8mm_P0.5mm_EP6.6x6.6mm,FT813Q-R,Bridgetek
"U8,U9",2,TLV76133DCY,Package_TO_SOT_SMD:SOT-223-3_TabPin2,TLV76133DCYR,Texas Instruments
U10,1,TPS61165-Q1,Package_TO_SOT_SMD:SOT-23-6,TPS61165-Q1,Texas Instruments
"U12,U13",2,TPS54202DDC,Package_TO_SOT_SMD:SOT-23-6,TPS542025DDCR,Texas Instruments

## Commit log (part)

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2026-02-15 creare proiect
2026-02-15 Conectori pe schematic
2026-02-15 Added 7segDispl parts
2026-02-17 Added LDO + LCD
2026-02-17 Updated NXP scheme
2026-02-17 Added Molex Connector
2026-02-17 Added mountingHoles
2026-02-17 Capacitors adjustment
2026-02-17 GPIO corrections
    Sheet is now ready for the first check.
2026-02-19 DSPL update version - Done
    + TestPins added
2026-02-20 Error corrections
2026-02-20 Reverse voltage protection added
    Additional:
    +4 mounting holes
    +corrected 1x resistor value
    +AUD pin connected by J2
2026-02-20 Protection update
2026-02-20 Updated Display Driver pins
2026-02-21 DWG cleanup
2026-02-21 BOM proto created
    bill of materials added without the parts identified
2026-02-21 RPP series added
2026-02-21 Added proto footprints for Layout
2026-02-21 Layout proto_check
2026-02-23 New BL chip proto
    New chip is currently placed but surrounding components not fine-selected
2026-02-23 BL drive correction
2026-02-24 PCL_Layout_Arrangements
    Initial PCB components arangement done.
    Not a functional version!
2026-02-24 Layout_Progress_0.1
2026-02-25 Layout_Progress_0.2
    + 7seg x8 Digits connected
    +LDO started
2026-02-25 Layout_progress_0.3
2026-02-26 Layout_progress_0.4
2026-02-27 VCU components displacement change
    +added NXP Pin locations
    +added precise LCD wire connectors location
    +change LDO location
    +Motherboard size correction (width changed)
2026-02-27 Routes auto-routing
2026-02-28 Displacement corrections
    No routing done
2026-02-28 Arrangement correction
2026-03-02 Supply & NXP re-config
2026-03-03 LCD CPU corrections 0.1
2026-03-04 pF capacitors placement correction
2026-03-05 Displ conn pinout change
2026-03-05 NXP flip configuration
    *NXP is now flipped with J2 connector closer
    *Supply TPH2 inserted back
    *Wiring almost done
2026-03-07 NXP added + J3/1 for supply
    *Corrections done on supply entrance for NXP : J3/1
    *CAN OUT added for parallel connection
2026-03-07 Regulators and audio organisation
2026-03-07 CANOUT+J3 added
2026-03-07 Wiring progress + Activation Button
2026-03-08 Updates on board
2026-03-08 LED resistance correction
2026-03-08 Wiring_proto_Done
    Initial version of wiring - Done;
    Needs to be ckecked
2026-03-09 Error corrections+Footprint MP done
2026-03-09 Symbol cleanUp
2026-03-09 DSPL PINconnector fail->corrected
    Pin numbers inversed due to unknown error
2026-03-09 Layout_Label arangements
2026-03-09 Save_before change(Flag1)
2026-03-10 CPU_Displacement change+routing
    Bigger change coming now.
    DSPL Chip now closer to connector
2026-03-11 Routing Supply+GND
2026-03-11 PCB-ready for Check
    Component placing - Done
    Wiring - Done;
    To be checkedk
2026-03-12 Before_ChipFlipVersion
2026-03-12 FT-Chip flip config
    Separate GND planes not done here.
2026-03-12 GND planes added
2026-03-13 OnlyChipFlipVersion
2026-03-14 Clock chip rotated+wired
2026-03-14 IRQ signal removed
2026-03-15 Wire routing_small change
2026-03-15 GNDA plane added(proto)
2026-03-15 Audio rotate+ GNDA plane separate
2026-03-16 Required_corr_0.1
2026-03-16 Required_corr_0.2
2026-03-16 Required_corr_0.3
2026-03-16 Required_corr_0.4
2026-03-16 Required_corr_0.5
2026-03-17 Required_corr_0.6
2026-03-18 Required_corr_0.7
2026-03-18 Required_corr_0.8
2026-03-18 Required_corr_0.9
2026-03-19 Required_corr_1.0
    *Changed wiring at Touchscreen connector
2026-03-19 Board size change 250x110 -> 250x107
2026-03-20 Required_corr_1.1
    *I2C wires
    *12V to NXP
    *LED wires removed - temporary
    *7seg Pullup res wires
2026-03-20 Schmitt_correction_0.1
2026-03-20 Audio_correction_0.1
2026-03-20 7seg+LED changes
2026-03-20 7seg Schematic edited
2026-03-21 All_wires_to_0.2mm
    All the wires had the size forced to 0.2mm
2026-03-21 Wires sized
2026-03-22 LED supply wires correction
2026-03-22 GND empty spot extension
2026-03-23 GND lines added + JST connector
2026-03-24 JST connectors added
2026-03-24 JST CAN connector change
2026-03-24 CAN GND removed
2026-03-24 BJT to MOS transfer + new LED
    NMOS Datasheet: https://www.onsemi.com/pdf/datasheet/bss138-d.pdf
    LED Datasheet: https://www.mouser.com/catalog/specsheets/ams%20OSRAM_04-30-2025_LS%20ETSF.01_EN.pdf?_gl=1*1llmkcu*_gcl_aw*R0NMLjE3NzI3MDEzNDUuQ2owS0NRandyczJYQmhEakFSSXNBSFZ5bW1UcjlpUWl6aF9Xd1RWYXh4L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
2026-03-24 New Pin assignment
2026-03-24 NMOS correction
2026-03-24 SHOTTKY x2 size change
2026-03-25 Added NXP board
2026-03-25 Logos_Added
2026-03-25 Gerber_files_created_V1.0
2026-03-25 NXP_correction for3D_Enclosure
2026-03-25 Gerber_settings_changed
2026-03-26 Revision_added
2026-03-26 MountingHoles:change to M3
2026-04-21 PartList_added
2026-04-21 LastBOM added
2026-04-21 new Gerbers
2026-04-21 JST-PA -4x 1x02 - added
2026-04-22 1x molex change in BOM
2026-05-02 Simulations_NIMultisim
2026-05-03 Simulations_0.2
2026-05-08 JST partNr. correction
    10129303-116001 B --> 10129383-116001 B
    10129303-120001 B --> 10129383-120001 B
    10129303-106001 B --> 10129383-106001 B
2026-05-26 Revision author added
2026-06-04 Touchscreen wiring - correction
2026-06-04 Logo+ Documentation changes
2026-06-05 Display connector GND change to solid GND
2026-06-06 Issues txt file added
    Issues of the PCB are written here for further correction
2026-06-06 Documentation refrezh
2026-06-08 Voltage regulator 12->7V added
    *Mounting holes replaced with simple holes
    *Resistances for power LED changed
2026-06-08 Logo correction
2026-06-09 Diode/L2/D16/etc. footprint size correction
2026-06-10 NewSupplyArchitecture - v0.1
2026-06-10 Backup versions added
2026-06-13 Shifting AUD 3V3 -> 5V0
2026-06-13 Major changes here
    *GND planes;
    *Supply paths
    *Chip crystal removed
    *Changes with INT/PD/SCK wiring
2026-06-14 AUDIO chip footprint corrected
    Footprint uploaded from Mouser for exact reference.
2026-06-16 GND planes correction
2026-06-17 DNP 0 Ohm resistors added
    DNP resistors added for the case where the Buck converters would have to be bridged.
    The DNP resistors are rated by their size: 1206 - 3.0A -> 4.0A that should be more than enough for this Board
2026-06-20 MainGND plane corrections
2026-06-20 Changes to touchscreen i2c and display power
2026-06-20 Check on E-plan
2026-06-22 BOM v2.0 - added
2026-06-24 Reworked audio area
2026-06-24 Reworked segments routing
2026-06-24 Revamped connections and ground planes for the rest of the PCB
2026-06-26 Removed GND guards
2026-06-27 V2.21
    Layout 1 ready
2026-06-27 Project closed
2026-06-27 AUDIO chip footprint correction
2026-06-28 Routing optimisations
2026-06-28 Jumper added+ GND Sharp edges removed
2026-06-28 Swapped capacitors for schmitt inverter
2026-06-28 BOM+GBR - added
2026-06-28 BOM & GBR - sent
2026-06-28 Layout Locked - Sent for print
